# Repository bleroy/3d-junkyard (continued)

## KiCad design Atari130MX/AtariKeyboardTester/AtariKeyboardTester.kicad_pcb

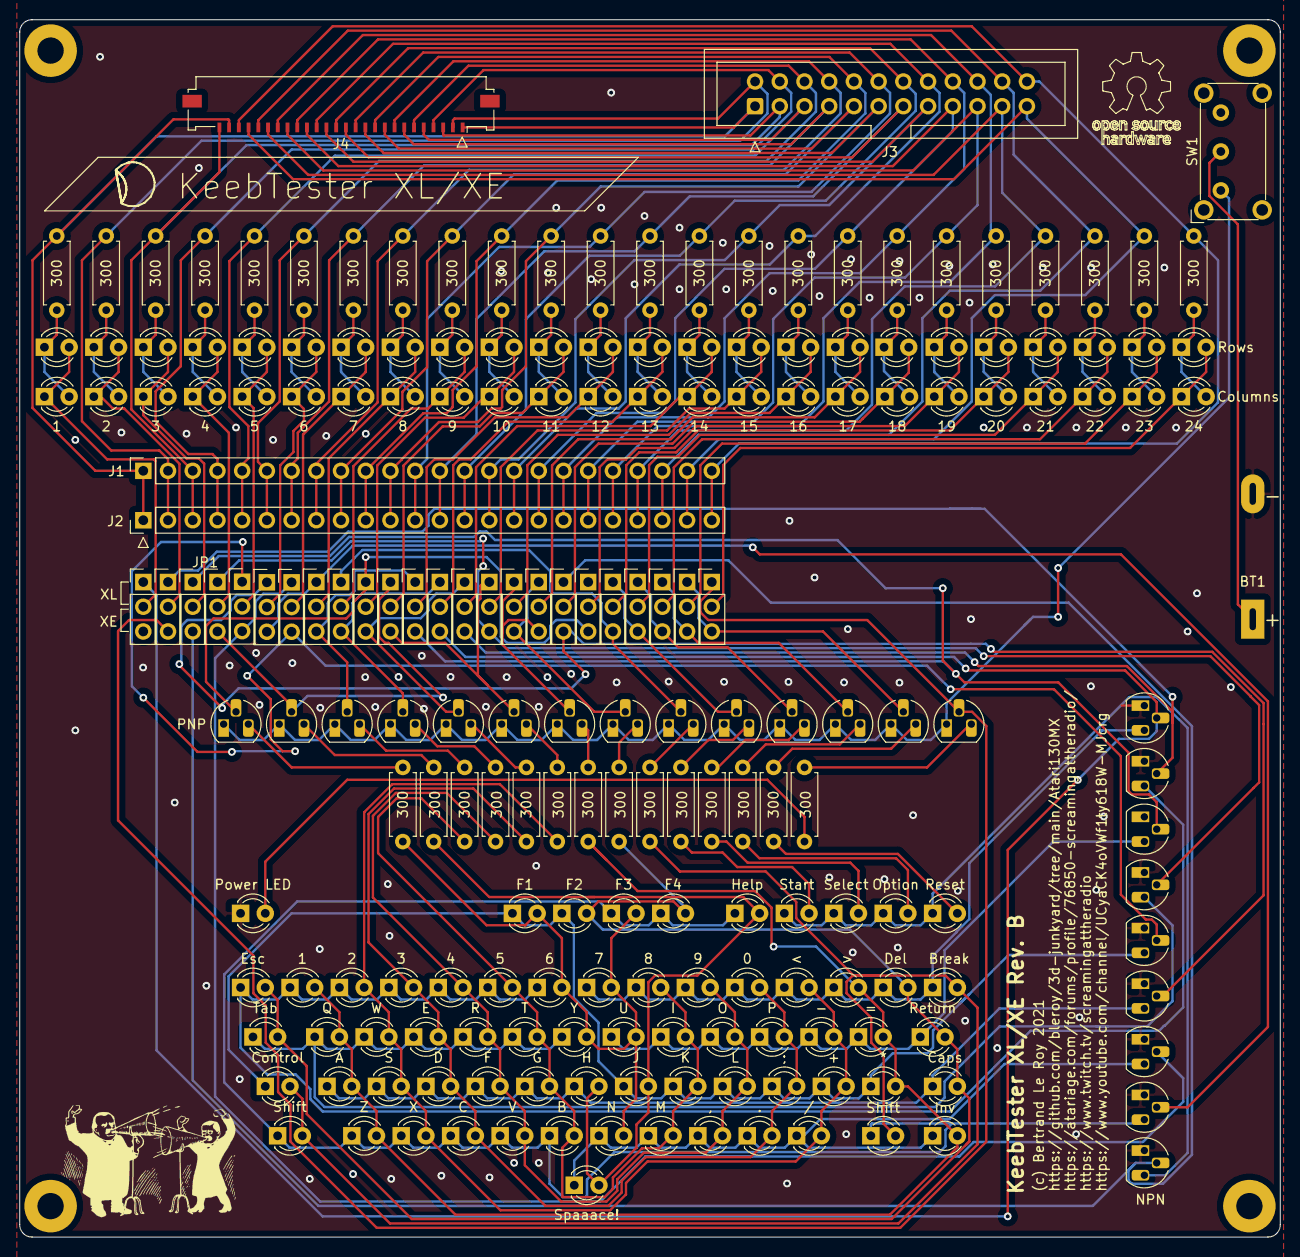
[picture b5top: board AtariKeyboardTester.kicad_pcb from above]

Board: 2 copper layers, 129.5 x 125.1 mm, 207 parts (1 on the bottom side), 135 nets.

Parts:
0, 1, 1#2, 2, 2#2, 3, 3#2, 4, 4#2, 5, 5#2, 6, 6#2, 7, 7#2, 8, 8#2, 9, 9#2, 10, 11, 12, 13, 14, 15, 16, 17, 18, 19, 20, 21, 22, 23, 24, .: LED; LED_D3.0mm
300, 300#2, 300#3, 300#4, 300#5, 300#6, 300#7, 300#8, 300#9, 300#10, 300#11, 300#12, 300#13, 300#14, 300#15, 300#16, 300#17, 300#18, 300#19, 300#20, 300#21, 300#22, 300#23, 300#24, 300#25, 300#26, 300#27, 300#28, 300#29, 300#30, 300#31, 300#32, 300#33, 300#34, 300#35: R; R100
*: LED; LED_D3.0mm
+: LED; LED_D3.0mm
,: LED; LED_D3.0mm
-: LED; LED_D3.0mm
/: LED; LED_D3.0mm
;: LED; LED_D3.0mm
<: LED; LED_D3.0mm
=: LED; LED_D3.0mm
>: LED; LED_D3.0mm
A: LED; LED_D3.0mm
B: LED; LED_D3.0mm
BT1: Battery; BatteryHolder_MPD_BA9VPC_1xPP3
Break: LED; LED_D3.0mm
C: LED; LED_D3.0mm
Caps: LED; LED_D3.0mm
Control: LED; LED_D3.0mm
D: LED; LED_D3.0mm
D_A_2, D_A_3, D_A_4, D_A_5, D_A_6, D_A_7, D_A_8, D_A_9, D_A_10, D_A_11, D_A_12, D_A_13, D_A_14, D_A_15, D_A_16, D_A_17, D_A_18, D_A_19, D_A_20, D_A_21, D_A_22, D_A_23, D_A_24, D_A_25: LED; LED_D3.0mm
Del: LED; LED_D3.0mm
E: LED; LED_D3.0mm
Esc: LED; LED_D3.0mm
F, F1, F2, F3, F4: LED; LED_D3.0mm
G: LED; LED_D3.0mm
H: LED; LED_D3.0mm
Help: LED; LED_D3.0mm
I: LED; LED_D3.0mm
Inv: LED; LED_D3.0mm
J: LED; LED_D3.0mm
J1: Conn_01x24; PinSocket_1x24_P2.54mm_Vertical
J2: Conn_01x24; PinHeader_1x24_P2.54mm_Vertical
J3: Conn_02x12_Odd_Even; IDC-Header_2x12_P2.54mm_Vertical
J4: Conn_01x26; Molex_200528-0260_1x26-1MP_P1.00mm_Horizontal
JP1, JP2, JP3, JP4, JP5, JP6, JP7, JP8, JP9, JP10, JP11, JP12, JP13, JP14, JP15, JP16, JP17, JP18, JP19, JP20, JP21, JP22, JP23, JP24: SolderJumper_3_Open; PinHeader_1x03_P2.54mm_Vertical
K: LED; LED_D3.0mm
L: LED; LED_D3.0mm
M: LED; LED_D3.0mm
Matrix: Atari_XL_XE_Matrix
N: LED; LED_D3.0mm
O: LED; LED_D3.0mm
Option: LED; LED_D3.0mm
P: LED; LED_D3.0mm
Power LED: LED; LED_D3.0mm
Q: LED; LED_D3.0mm
Q_COL_1, Q_COL_2, Q_COL_3, Q_COL_4, Q_COL_5, Q_COL_6, Q_COL_7, Q_COL_8, Q_COL_9, Q_COL_10, Q_COL_11, Q_COL_12, Q_COL_13, Q_COL_14: Q_PNP_EBC; TO-92_HandSolder
Q_ROW_1, Q_ROW_2, Q_ROW_3, Q_ROW_4, Q_ROW_5, Q_ROW_6, Q_ROW_7, Q_ROW_8, Q_ROW_9: Q_NPN_EBC; TO-92_HandSolder
R: LED; LED_D3.0mm
R1, R2, R3: 300; R100
Reset: LED; LED_D3.0mm
Return: LED; LED_D3.0mm
S: LED; LED_D3.0mm
SW1: SW_SPST; SW_E-Switch_EG1224_SPDT_Angled
Select: LED; LED_D3.0mm
Shift: LED; LED_D3.0mm
Shift#2: LED; LED_D3.0mm
Spaaace!: LED; LED_D3.0mm
Start: LED; LED_D3.0mm
T: LED; LED_D3.0mm
Tab: LED; LED_D3.0mm
U: LED; LED_D3.0mm
V: LED; LED_D3.0mm
W: LED; LED_D3.0mm
X: LED; LED_D3.0mm
Y: LED; LED_D3.0mm
Z: LED; LED_D3.0mm

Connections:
B_CONN_1: 1.1, D_A_2.2, JP1.2
B_CONN_2: 2.1, D_A_3.2, JP2.2
B_CONN_3: 3.1, D_A_4.2, JP3.2
B_CONN_4: 4.1, D_A_5.2, JP4.2
B_CONN_5: 5.1, D_A_6.2, JP5.2
B_CONN_6: 6.1, D_A_7.2, JP6.2
B_CONN_7: 7.1, D_A_8.2, JP7.2
B_CONN_8: 8.1, D_A_9.2, JP8.2
B_CONN_9: 9.1, D_A_10.2, JP9.2
B_CONN_10: 10.1, D_A_11.2, JP10.2
B_CONN_11: 11.1, D_A_12.2, JP11.2
B_CONN_12: 12.1, D_A_13.2, JP12.2
B_CONN_13: 13.1, D_A_14.2, JP13.2
B_CONN_14: 14.1, D_A_15.2, JP14.2
B_CONN_15: 15.1, D_A_16.2, JP15.2
B_CONN_16: 16.1, D_A_17.2, JP16.2
B_CONN_17: 17.1, D_A_18.2, JP17.2
B_CONN_18: 18.1, D_A_19.2, JP18.2
B_CONN_19: 19.1, D_A_20.2, JP19.2
B_CONN_20: 20.1, D_A_21.2, JP20.2
B_CONN_21: 21.1, D_A_22.2, JP21.2
B_CONN_22: 22.1, D_A_23.2, JP22.2
B_CONN_23: 23.1, D_A_24.2, JP23.2
B_CONN_24: 24.1, D_A_25.2, JP24.2
COL_1: JP10.1, JP19.3, Q_COL_1.2
COL_2: JP4.3, JP11.1, Q_COL_2.2
COL_3: JP8.3, JP12.1, Q_COL_3.2
COL_4: JP9.3, JP13.1, Q_COL_4.2
COL_5: JP10.3, JP14.1, Q_COL_5.2
COL_6: JP11.3, JP15.1, Q_COL_6.2
COL_7: JP16.1, JP17.3, Q_COL_7.2
COL_8: JP16.3, JP17.1, Q_COL_8.2
COL_9: JP9.1, JP20.3, Q_COL_9.2
COL_10: JP20.1, JP21.3, Q_COL_10.2
COL_11: JP21.1, JP22.3, Q_COL_11.2
COL_12: JP22.1, JP23.3, Q_COL_12.2
COL_13: JP23.1, JP24.3, Q_COL_13.2
COL_14: JP2.3, JP24.1, Q_COL_14.2
CONN_1: J1.1, J2.1, J3.1, J4.1, J4.25, R1.2
CONN_2: J1.2, J2.2, J3.2, J4.2, R2.2
CONN_3: J1.3, J2.3, J3.3, J4.3, J4.26, R3.2
CONN_4: 300#33.2, J1.4, J2.4, J3.4, J4.4
CONN_5: 300.2, J1.5, J2.5, J3.5, J4.5
CONN_6: 300#2.2, J1.6, J2.6, J3.6, J4.6
CONN_7: 300#3.2, J1.7, J2.7, J3.7, J4.7
CONN_8: 300#4.2, J1.8, J2.8, J3.8, J4.8
CONN_9: 300#5.2, J1.9, J2.9, J3.9, J4.9
CONN_10: 300#6.2, J1.10, J2.10, J3.10, J4.10
CONN_11: 300#7.2, J1.11, J2.11, J3.11, J4.11
CONN_12: 300#8.2, J1.12, J2.12, J3.12, J4.12
CONN_13: 300#9.2, J1.13, J2.13, J3.13, J4.13
CONN_14: 300#10.2, J1.14, J2.14, J3.14, J4.14
CONN_15: 300#11.2, J1.15, J2.15, J3.15, J4.15
CONN_16: 300#12.2, J1.16, J2.16, J3.16, J4.16
CONN_17: 300#13.2, J1.17, J2.17, J3.17, J4.17
CONN_18: 300#14.2, J1.18, J2.18, J3.18, J4.18
CONN_19: 300#15.2, J1.19, J2.19, J3.19, J4.19
CONN_20: 300#16.2, J1.20, J2.20, J3.20, J4.20
CONN_21: 300#17.2, J1.21, J2.21, J3.21, J4.21
CONN_22: 300#18.2, J1.22, J2.22, J3.22, J4.22
CONN_23: 300#34.2, J1.23, J2.23, J3.23, J4.23
CONN_24: 300#19.2, J1.24, J2.24, J3.24, J4.24
GND: BT1.2, Power LED.1, Q_ROW_1.1, Q_ROW_2.1, Q_ROW_3.1, Q_ROW_4.1, Q_ROW_5.1, Q_ROW_6.1, Q_ROW_7.1, Q_ROW_8.1, Q_ROW_9.1
LED_COL_1: 6#2.2, 7#2.2, 300#20.2, F1.2, F3.2, N.2, U.2, Y.2
LED_COL_2: 300#21.2, H.2, Help.2, J.2, Spaaace!.2
LED_COL_3: 5#2.2, 8#2.2, 300#22.2, B.2, G.2, I.2, K.2, M.2, T.2
LED_COL_4: 4#2.2, 9#2.2, 300#23.2, ,.2, F.2, L.2, O.2, R.2, V.2
LED_COL_5: 0.2, 3#2.2, 300#24.2, ..2, ;.2, C.2, D.2, E.2, P.2
LED_COL_6: 2#2.2, 300#25.2, +.2, -.2, /.2, <.2, S.2, W.2, X.2
LED_COL_7: 1#2.2, 300#26.2, *.2, =.2, >.2, A.2, Inv.2, Q.2, Z.2
LED_COL_8: 300#35.2, Caps.2, Del.2, Esc.2, F2.2, F4.2, Return.2, Tab.2
LED_COL_9: 300#27.2, Break.2, Control.2, Shift.2, Shift#2.2
LED_COL_10: 300#28.2, Start.2
LED_COL_11: 300#29.2, Select.2
LED_COL_12: 300#30.2, Option.2
LED_COL_13: 300#31.2, Reset.2
LED_COL_14: 300#32.2, Power LED.2
LED_ROW_1: 0.1, 7#2.1, 8#2.1, 9#2.1, <.1, >.1, Break.1, Del.1, Q_ROW_1.3
LED_ROW_2: 1#2.1, 2#2.1, 3#2.1, 4#2.1, 5#2.1, 6#2.1, Esc.1, Q_ROW_2.3
LED_ROW_3: -.1, =.1, I.1, O.1, P.1, Q_ROW_3.3, Return.1, U.1
LED_ROW_4: E.1, Q.1, Q_ROW_4.3, R.1, T.1, Tab.1, W.1, Y.1
LED_ROW_5: *.1, +.1, ;.1, Control.1, F1.1, F2.1, J.1, K.1, L.1, Q_ROW_5.3
LED_ROW_6: A.1, Caps.1, D.1, F.1, G.1, H.1, Q_ROW_6.3, S.1
LED_ROW_7: ,.1, ..1, /.1, Inv.1, M.1, N.1, Q_ROW_7.3, Spaaace!.1
LED_ROW_8: B.1, C.1, F3.1, F4.1, Help.1, Q_ROW_8.3, Shift.1, Shift#2.1, V.1, X.1, Z.1
LED_ROW_9: Option.1, Q_ROW_9.3, Reset.1, Select.1, Start.1
unnamed: BT1.1, SW1.2
unnamed: 1.2, D_A_2.1, R1.1
unnamed: 2.2, D_A_3.1, R2.1
unnamed: 3.2, D_A_4.1, R3.1
unnamed: 4.2, 300#33.1, D_A_5.1
unnamed: 5.2, 300.1, D_A_6.1
unnamed: 6.2, 300#2.1, D_A_7.1
unnamed: 7.2, 300#3.1, D_A_8.1
unnamed: 8.2, 300#4.1, D_A_9.1
unnamed: 9.2, 300#5.1, D_A_10.1
unnamed: 10.2, 300#6.1, D_A_11.1
unnamed: 11.2, 300#7.1, D_A_12.1
unnamed: 12.2, 300#8.1, D_A_13.1
unnamed: 13.2, 300#9.1, D_A_14.1
unnamed: 14.2, 300#10.1, D_A_15.1
unnamed: 15.2, 300#11.1, D_A_16.1
unnamed: 16.2, 300#12.1, D_A_17.1
unnamed: 17.2, 300#13.1, D_A_18.1
unnamed: 18.2, 300#14.1, D_A_19.1
unnamed: 19.2, 300#15.1, D_A_20.1
unnamed: 20.2, 300#16.1, D_A_21.1
unnamed: 21.2, 300#17.1, D_A_22.1
unnamed: 22.2, 300#18.1, D_A_23.1
unnamed: 23.2, 300#34.1, D_A_24.1
unnamed: 24.2, 300#19.1, D_A_25.1
unnamed: 300#20.1, Q_COL_1.3
unnamed: 300#21.1, Q_COL_2.3
unnamed: 300#22.1, Q_COL_3.3
unnamed: 300#23.1, Q_COL_4.3
unnamed: 300#24.1, Q_COL_5.3
unnamed: 300#25.1, Q_COL_6.3
unnamed: 300#26.1, Q_COL_7.3
unnamed: 300#35.1, Q_COL_8.3
unnamed: 300#27.1, Q_COL_9.3
unnamed: 300#28.1, Q_COL_10.3
unnamed: 300#29.1, Q_COL_11.3
unnamed: 300#30.1, Q_COL_12.3
unnamed: 300#31.1, Q_COL_13.3
unnamed: 300#32.1, Q_COL_14.3
ROW_1: JP1.1, JP13.3, Q_ROW_1.2
ROW_2: JP2.1, JP14.3, Q_ROW_2.2
ROW_3: JP3.1, JP12.3, Q_ROW_3.2
ROW_4: JP4.1, JP15.3, Q_ROW_4.2
ROW_5: JP5.1, JP7.3, Q_ROW_5.2
ROW_6: JP6.1, JP18.3, Q_ROW_6.2
ROW_7: JP5.3, JP7.1, Q_ROW_7.2
ROW_8: JP6.3, JP8.1, Q_ROW_8.2
ROW_9: JP3.3, JP18.1, Q_ROW_9.2
VCC: Q_COL_1.1, Q_COL_2.1, Q_COL_3.1, Q_COL_4.1, Q_COL_5.1, Q_COL_6.1, Q_COL_7.1, Q_COL_8.1, Q_COL_9.1, Q_COL_10.1, Q_COL_11.1, Q_COL_12.1, Q_COL_13.1, Q_COL_14.1, SW1.1
